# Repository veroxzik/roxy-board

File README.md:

# roxy-board
 The schematic and layout files for Roxy.

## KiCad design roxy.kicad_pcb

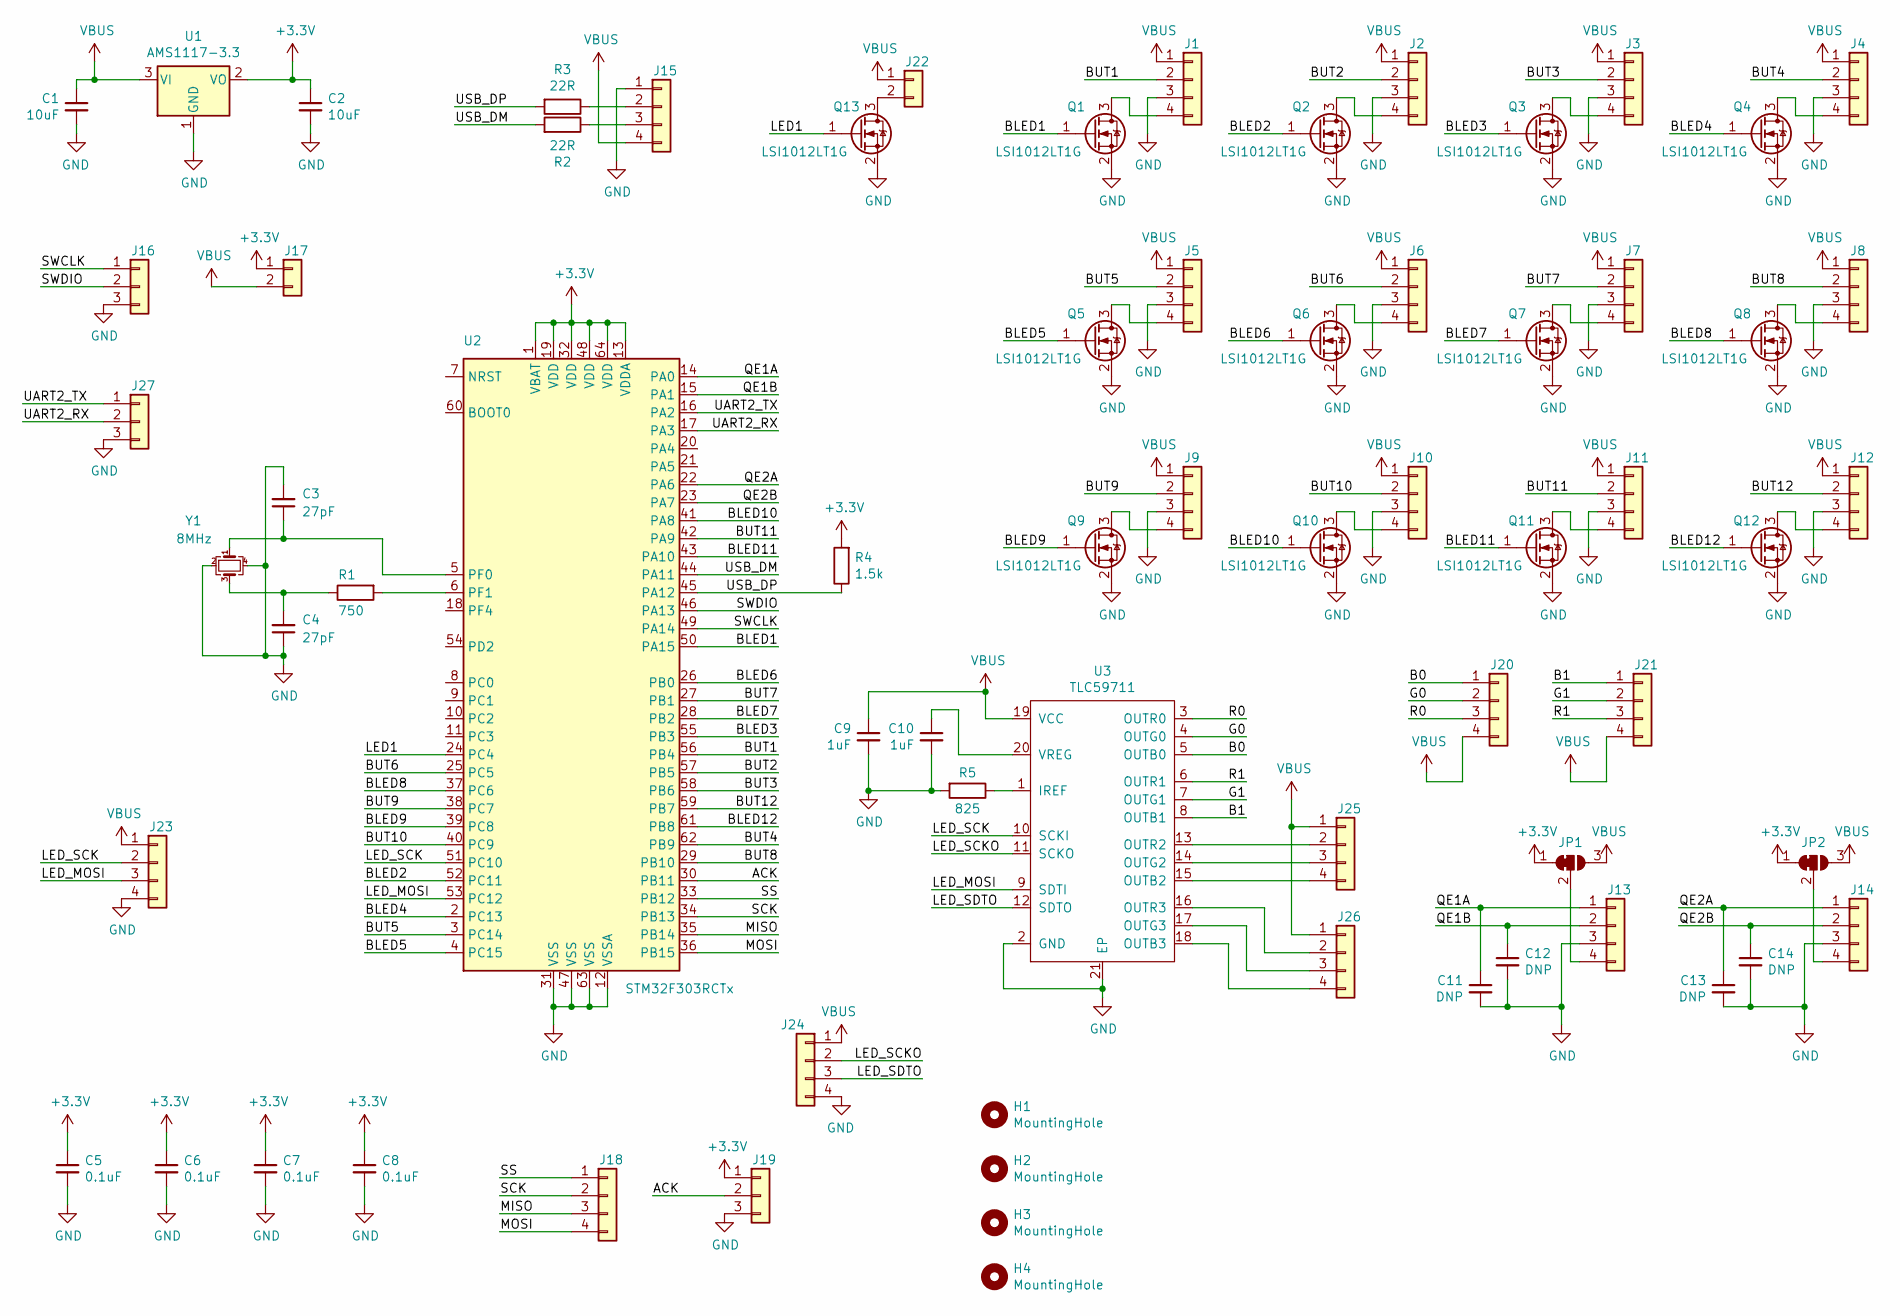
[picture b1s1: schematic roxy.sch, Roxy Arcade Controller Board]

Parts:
C1, C2: 10uF; C_0805_2012Metric_Pad1.15x1.40mm_HandSolder
C3, C4: 27pF; C_0603_1608Metric
C5, C6, C7, C8: 0.1uF; C_0603_1608Metric_Pad1.05x0.95mm_HandSolder
C9, C10: 1uF; C_0603_1608Metric_Pad1.05x0.95mm_HandSolder
C11, C12, C13, C14: DNP; C_0603_1608Metric_Pad1.05x0.95mm_HandSolder
H1, H2, H3, H4: MountingHole; MountingHole_3.2mm_M3_ISO14580
J1, J2, J3, J4, J5, J6, J7, J8, J9, J10, J11, J12, J13, J14, J15, J20, J21, J24: Conn_01x04; JST_XH_B4B-XH-AM_1x04_P2.50mm_Vertical
J16, J19, J27: DNP; PinHeader_1x03_P2.54mm_Vertical
J17: DNP; PinHeader_1x02_P2.54mm_Vertical
J18, J23: DNP; PinHeader_1x04_P2.54mm_Vertical
J22: Conn_01x02; JST_XH_B2B-XH-AM_1x02_P2.50mm_Vertical
J25, J26: DNP; PinHeader_1x04_P2.00mm_Vertical
JP1, JP2: SolderJumper_3_Bridged12; SolderJumper-3_P1.3mm_Bridged12_RoundedPad1.0x1.5mm
Q1, Q2, Q3, Q4, Q5, Q6, Q7, Q8, Q9, Q10, Q11, Q12, Q13: LSI1012LT1G; SOT-23
R1: 750; R_0603_1608Metric
R2, R3: 22R; R_0603_1608Metric
R4: 1.5k; R_0603_1608Metric
R5: 825; R_0603_1608Metric_Pad1.05x0.95mm_HandSolder
U1: AMS1117-3.3; SOT-223-3_TabPin2
U2: STM32F303RCTx; LQFP-64_10x10mm_P0.5mm
U3: TLC59711; HTSSOP-20-1EP_4.4x6.5mm_P0.65mm_EP3.4x6.5mm_Mask2.75x3.43mm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
Y1: 8MHz; Crystal_SMD_5032-4Pin_5.0x3.2mm

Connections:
+3V3: C2.1, C5.1, C6.1, C7.1, C8.1, J17.1, J19.1, JP1.1 (A), JP2.1 (A), R4.2, U1.2 (VO), U2.1 (VBAT), U2.13 (VDDA), U2.19 (VDD), U2.32 (VDD), U2.48 (VDD), U2.64 (VDD)
/ACK: J19.2, U2.30 (PB11)
/B0: J20.1, U3.5 (OUTB0)
/B1: J21.1, U3.8 (OUTB1)
/BLED1: Q1.1 (G), U2.50 (PA15)
/BLED2: Q2.1 (G), U2.52 (PC11)
/BLED3: Q3.1 (G), U2.55 (PB3)
/BLED4: Q4.1 (G), U2.2 (PC13)
/BLED5: Q5.1 (G), U2.4 (PC15)
/BLED6: Q6.1 (G), U2.26 (PB0)
/BLED7: Q7.1 (G), U2.28 (PB2)
/BLED8: Q8.1 (G), U2.37 (PC6)
/BLED9: Q9.1 (G), U2.39 (PC8)
/BLED10: Q10.1 (G), U2.41 (PA8)
/BLED11: Q11.1 (G), U2.43 (PA10)
/BLED12: Q12.1 (G), U2.61 (PB8)
/BUT1: J1.2, U2.56 (PB4)
/BUT2: J2.2, U2.57 (PB5)
/BUT3: J3.2, U2.58 (PB6)
/BUT4: J4.2, U2.62 (PB9)
/BUT5: J5.2, U2.3 (PC14)
/BUT6: J6.2, U2.25 (PC5)
/BUT7: J7.2, U2.27 (PB1)
/BUT8: J8.2, U2.29 (PB10)
/BUT9: J9.2, U2.38 (PC7)
/BUT10: J10.2, U2.40 (PC9)
/BUT11: J11.2, U2.42 (PA9)
/BUT12: J12.2, U2.59 (PB7)
/G0: J20.2, U3.4 (OUTG0)
/G1: J21.2, U3.7 (OUTG1)
/LED1: Q13.1 (G), U2.24 (PC4)
/LED_MOSI: J23.3, U2.53 (PC12), U3.9 (SDTI)
/LED_SCK: J23.2, U2.51 (PC10), U3.10 (SCKI)
/LED_SCKO: J24.2, U3.11 (SCKO)
/LED_SDTO: J24.3, U3.12 (SDTO)
/MISO: J18.3, U2.35 (PB14)
/MOSI: J18.4, U2.36 (PB15)
/QE1A: C11.1, J13.1, U2.14 (PA0)
/QE1B: C12.1, J13.2, U2.15 (PA1)
/QE2A: C13.1, J14.1, U2.22 (PA6)
/QE2B: C14.1, J14.2, U2.23 (PA7)
/R0: J20.3, U3.3 (OUTR0)
/R1: J21.3, U3.6 (OUTR1)
/SCK: J18.2, U2.34 (PB13)
/SS: J18.1, U2.33 (PB12)
/SWCLK: J16.1, U2.49 (PA14)
/SWDIO: J16.2, U2.46 (PA13)
/UART2_RX: J27.2, U2.17 (PA3)
/UART2_TX: J27.1, U2.16 (PA2)
/USB_DM: R2.2, U2.44 (PA11)
/USB_DP: R3.2, R4.1, U2.45 (PA12)
GND: C1.2, C2.2, C3.2, C4.1, C5.2, C6.2, C7.2, C8.2, C9.2, C10.2, C11.2, C12.2, C13.2, C14.2, J1.3, J2.3, J3.3, J4.3, J5.3, J6.3, J7.3, J8.3, J9.3, J10.3, J11.3, J12.3, J13.3, J14.3, J15.1, J16.3, J19.3, J23.4, J24.4, J27.3, Q1.2 (S), Q2.2 (S), Q3.2 (S), Q4.2 (S), Q5.2 (S), Q6.2 (S), Q7.2 (S), Q8.2 (S), Q9.2 (S), Q10.2 (S), Q11.2 (S), Q12.2 (S), Q13.2 (S), R5.2, U1.1 (GND), U2.12 (VSSA), U2.31 (VSS), U2.47 (VSS), U2.63 (VSS), U3.2 (GND), U3.21 (EP), Y1.2, Y1.4
unnamed: C3.1, U2.5 (PF0), Y1.1
unnamed: C4.2, R1.1, Y1.3
unnamed: C10.1, U3.20 (VREG)
unnamed: J1.4, Q1.3 (D)
unnamed: J2.4, Q2.3 (D)
unnamed: J3.4, Q3.3 (D)
unnamed: J4.4, Q4.3 (D)
unnamed: J5.4, Q5.3 (D)
unnamed: J6.4, Q6.3 (D)
unnamed: J7.4, Q7.3 (D)
unnamed: J8.4, Q8.3 (D)
unnamed: J9.4, Q9.3 (D)
unnamed: J10.4, Q10.3 (D)
unnamed: J11.4, Q11.3 (D)
unnamed: J12.4, Q12.3 (D)
unnamed: J13.4, JP1.2 (C)
unnamed: J14.4, JP2.2 (C)
unnamed: J15.2, R3.1
unnamed: J15.3, R2.1
unnamed: J22.2, Q13.3 (D)
unnamed: J25.2, U3.13 (OUTR2)
unnamed: J25.3, U3.14 (OUTG2)
unnamed: J25.4, U3.15 (OUTB2)
unnamed: J26.2, U3.16 (OUTR3)
unnamed: J26.3, U3.17 (OUTG3)
unnamed: J26.4, U3.18 (OUTB3)
unnamed: R1.2, U2.6 (PF1)
unnamed: R5.1, U3.1 (IREF)
VBUS: C1.1, C9.1, J1.1, J2.1, J3.1, J4.1, J5.1, J6.1, J7.1, J8.1, J9.1, J10.1, J11.1, J12.1, J15.4, J17.2, J20.4, J21.4, J22.1, J23.1, J24.1, J25.1, J26.1, JP1.3 (B), JP2.3 (B), U1.3 (VI), U3.19 (VCC)

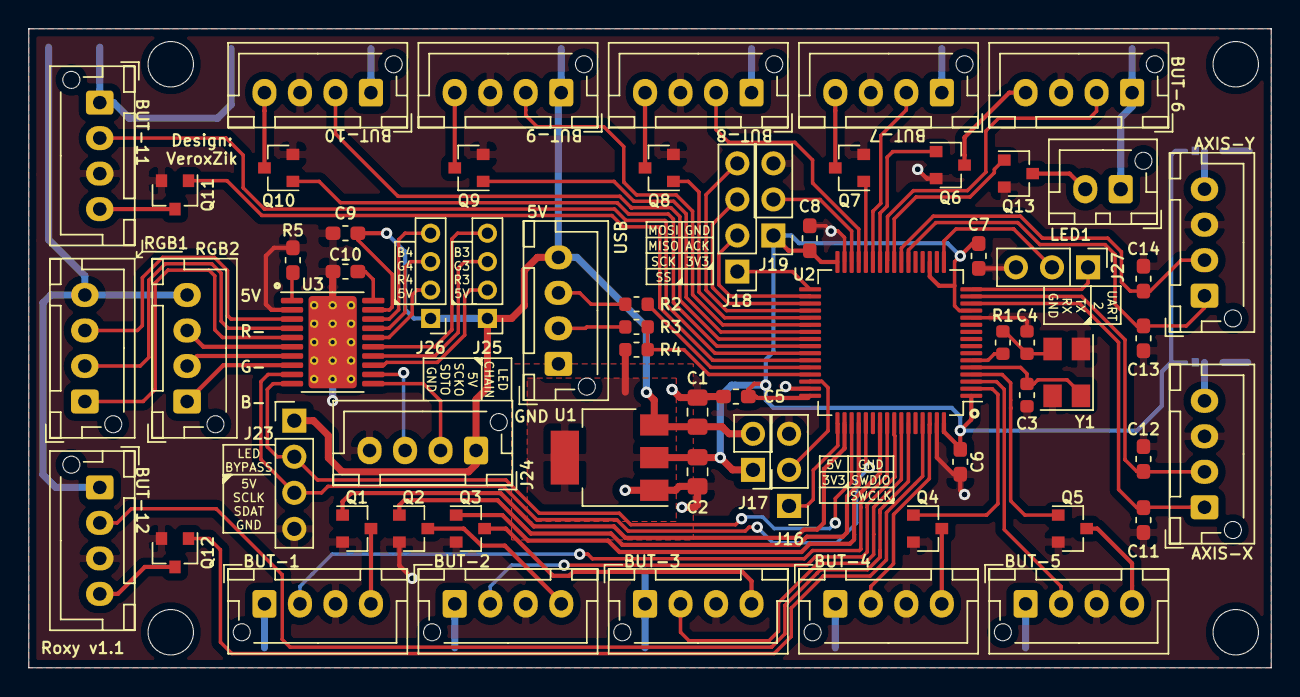
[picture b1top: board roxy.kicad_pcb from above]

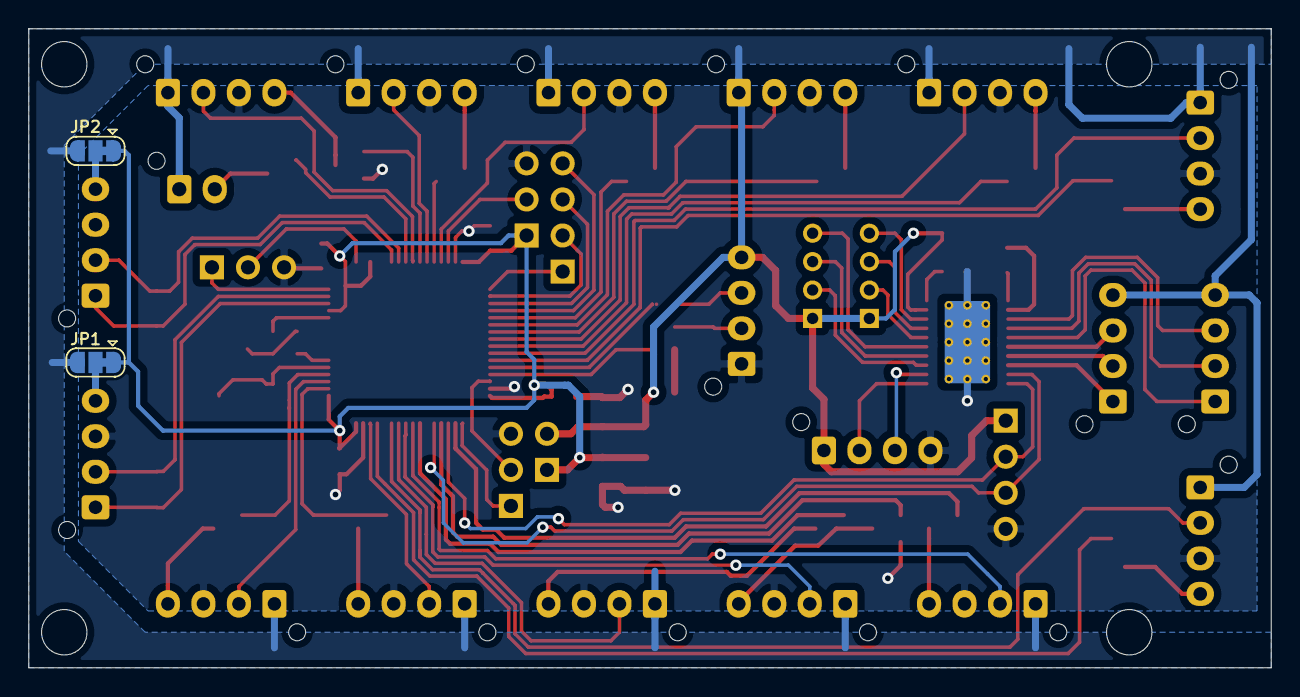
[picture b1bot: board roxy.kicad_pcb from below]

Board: 2 copper layers, 87.5 x 45.0 mm, 69 parts (2 on the bottom side), 81 nets.

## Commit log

2020-07-19 Commit v1.1
